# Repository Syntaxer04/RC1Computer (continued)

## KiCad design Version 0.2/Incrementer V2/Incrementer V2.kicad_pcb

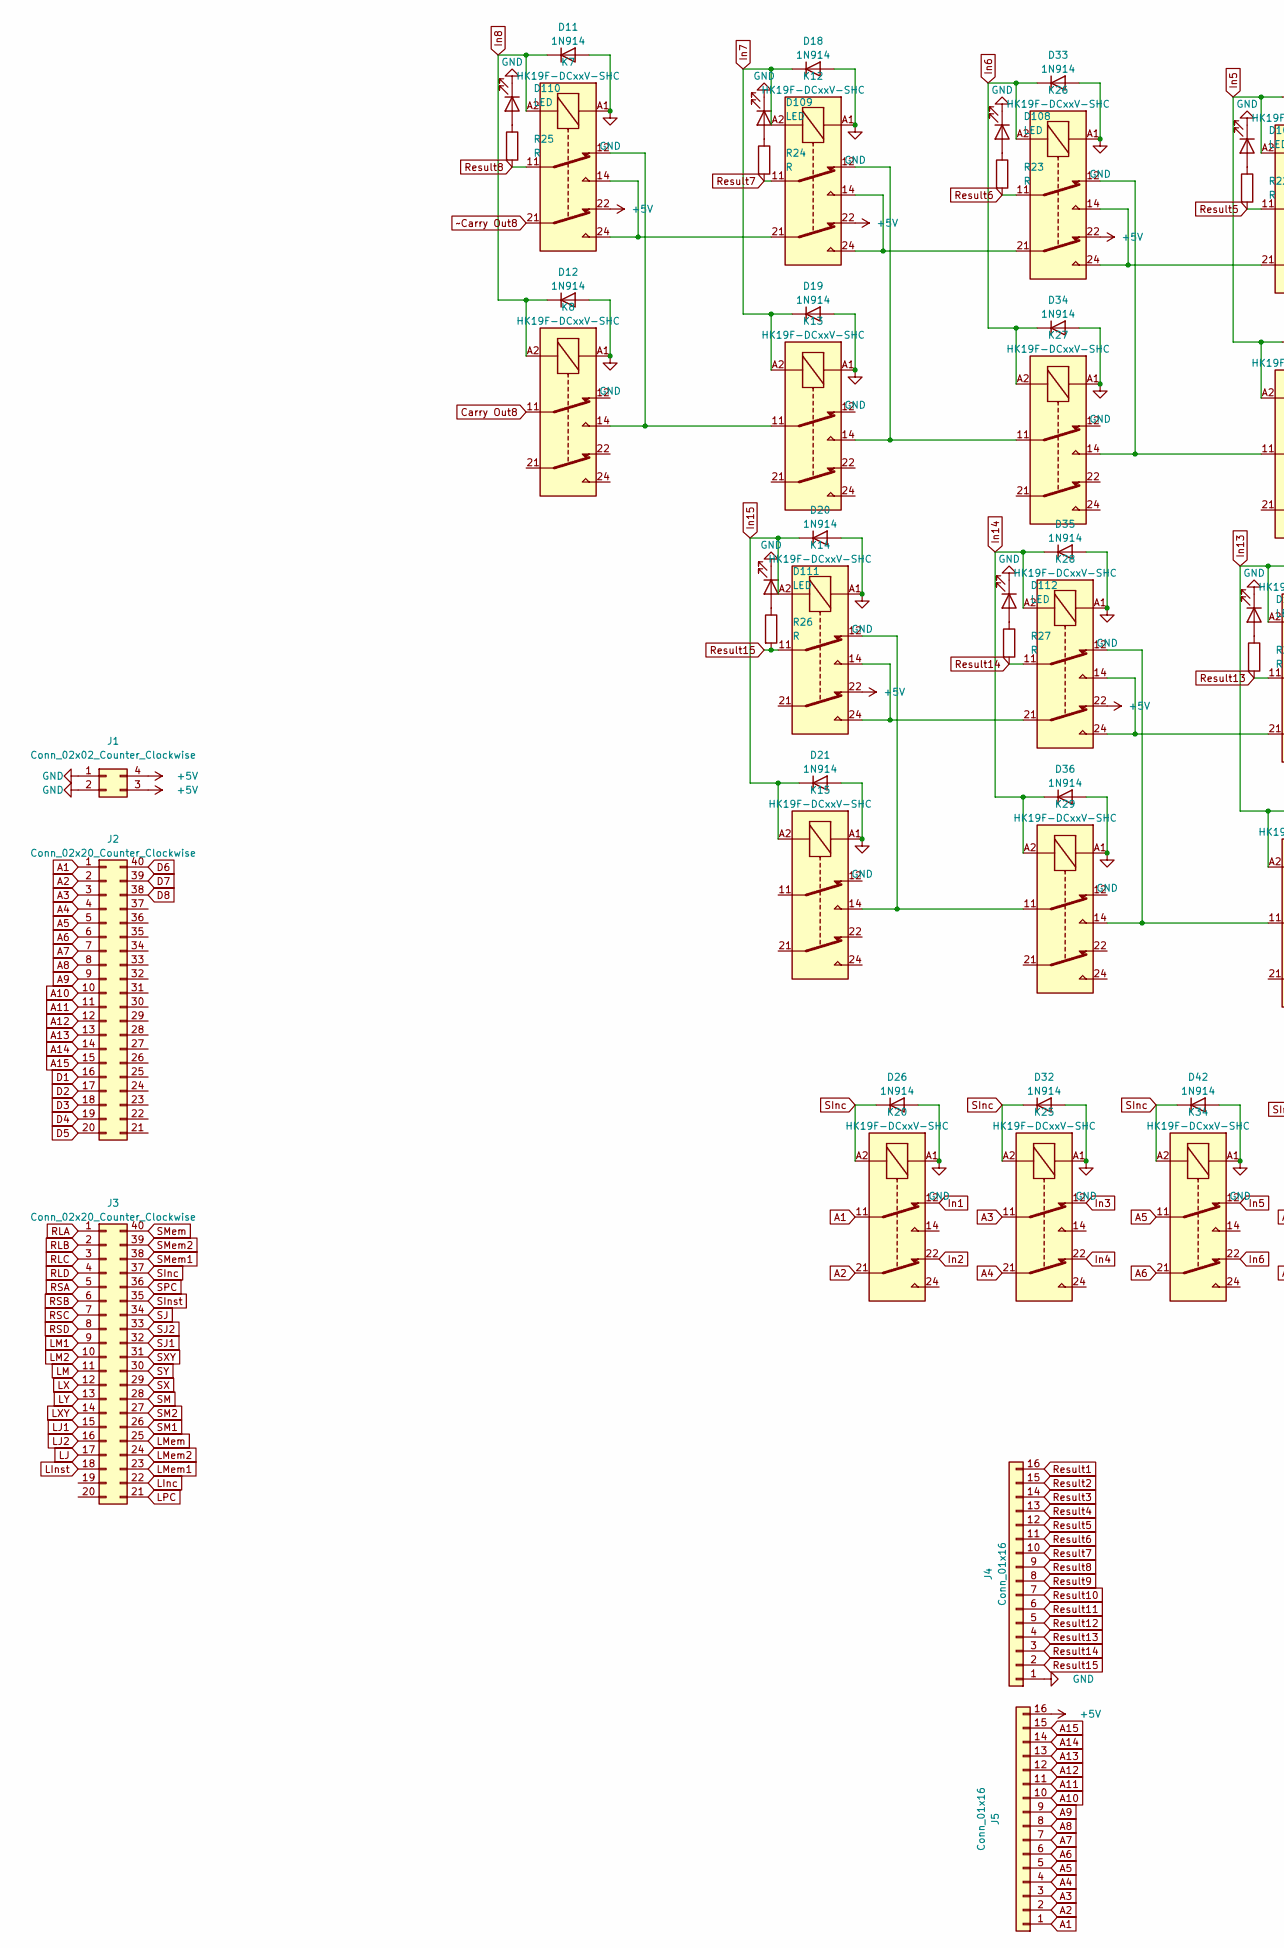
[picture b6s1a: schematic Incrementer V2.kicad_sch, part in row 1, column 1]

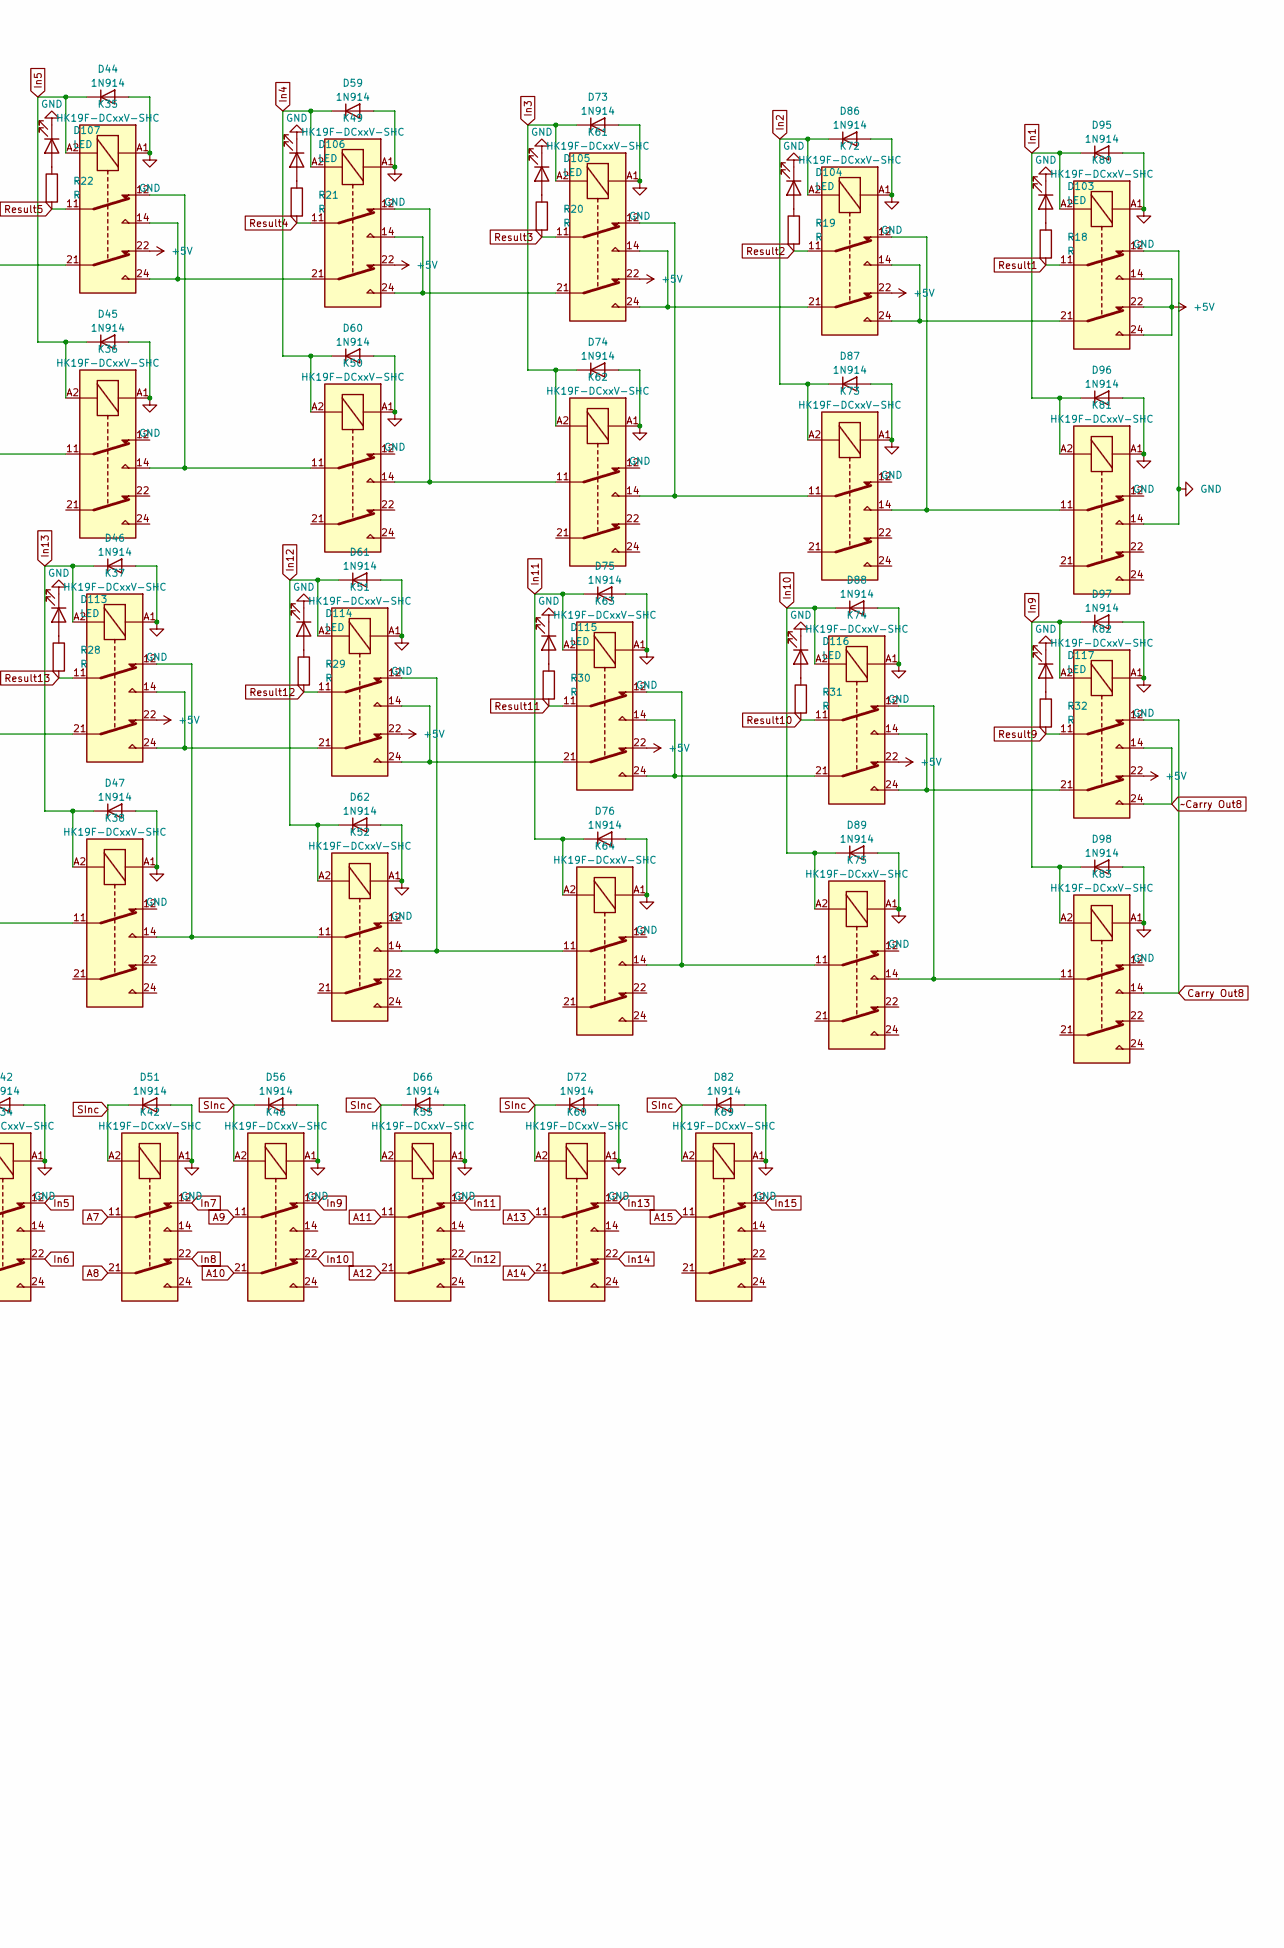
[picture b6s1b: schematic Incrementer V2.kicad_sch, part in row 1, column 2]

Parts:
D11, D12, D18, D19, D20, D21, D26, D32, D33, D34, D35, D36, D42, D44, D45, D46, D47, D51, D56, D59, D60, D61, D62, D66, D72, D73, D74, D75, D76, D82, D86, D87, D88, D89, D95, D96, D97, D98: 1N914; D_DO-35_SOD27_P7.62mm_Horizontal
D103, D104, D105, D106, D107, D108, D109, D110, D111, D112, D113, D114, D115, D116, D117: LED; LED_D5.0mm ohne SilkS
J1: Conn_02x02_Counter_Clockwise; PinSocket_2x02_P2.54mm_Horizontal
J2, J3: Conn_02x20_Counter_Clockwise; PinSocket_2x20_P2.54mm_Horizontal
J4, J5: Conn_01x16; PinHeader_1x16_P2.54mm_Vertical
K7, K8, K12, K13, K14, K15, K20, K25, K26, K27, K28, K29, K34, K35, K36, K37, K38, K42, K46, K49, K50, K51, K52, K55, K60, K61, K62, K63, K64, K69, K72, K73, K74, K75, K80, K81, K82, K83: HK19F-DCxxV-SHC; Relay_DPDT_Finder_30.22 ohne SilkS
R18, R19, R20, R21, R22, R23, R24, R25, R26, R27, R28, R29, R30, R31, R32: R; R_Axial_DIN0204_L3.6mm_D1.6mm_P7.62mm_Horizontal

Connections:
+5V: J1.3, J1.4, J5.16, K7.22, K12.22, K14.22, K26.22, K28.22, K35.22, K37.22, K49.22, K51.22, K61.22, K63.22, K72.22, K74.22, K80.14, K80.22, K80.24, K82.22
A1: J2.1, J5.1, K20.11
A2: J2.2, J5.2, K20.21
A3: J2.3, J5.3, K25.11
A4: J2.4, J5.4, K25.21
A5: J2.5, J5.5, K34.11
A6: J2.6, J5.6, K34.21
A7: J2.7, J5.7, K42.11
A8: J2.8, J5.8, K42.21
A9: J2.9, J5.9, K46.11
A10: J2.10, J5.10, K46.21
A11: J2.11, J5.11, K55.11
A12: J2.12, J5.12, K55.21
A13: J2.13, J5.13, K60.11
A14: J2.14, J5.14, K60.21
A15: J2.15, J5.15, K69.11
Carry Out8: K8.11, K82.12, K83.14
D1: J2.16
D2: J2.17
D3: J2.18
D4: J2.19
D5: J2.20
D6: J2.40
D7: J2.39
D8: J2.38
GND: D11.2 (A), D12.2 (A), D18.2 (A), D19.2 (A), D20.2 (A), D21.2 (A), D26.2 (A), D32.2 (A), D33.2 (A), D34.2 (A), D35.2 (A), D36.2 (A), D42.2 (A), D44.2 (A), D45.2 (A), D46.2 (A), D47.2 (A), D51.2 (A), D56.2 (A), D59.2 (A), D60.2 (A), D61.2 (A), D62.2 (A), D66.2 (A), D72.2 (A), D73.2 (A), D74.2 (A), D75.2 (A), D76.2 (A), D82.2 (A), D86.2 (A), D87.2 (A), D88.2 (A), D89.2 (A), D95.2 (A), D96.2 (A), D97.2 (A), D98.2 (A), D103.1 (K), D104.1 (K), D105.1 (K), D106.1 (K), D107.1 (K), D108.1 (K), D109.1 (K), D110.1 (K), D111.1 (K), D112.1 (K), D113.1 (K), D114.1 (K), D115.1 (K), D116.1 (K), D117.1 (K), J1.1, J1.2, J4.1, K7.A1, K8.A1, K12.A1, K13.A1, K14.A1, K15.A1, K20.A1, K25.A1, K26.A1, K27.A1, K28.A1, K29.A1, K34.A1, K35.A1, K36.A1, K37.A1, K38.A1, K42.A1, K46.A1, K49.A1, K50.A1, K51.A1, K52.A1, K55.A1, K60.A1, K61.A1, K62.A1, K63.A1, K64.A1, K69.A1, K72.A1, K73.A1, K74.A1, K75.A1, K80.12, K80.A1, K81.14, K81.A1, K82.A1, K83.A1
In1: D95.1 (K), D96.1 (K), K20.12, K80.A2, K81.A2
In2: D86.1 (K), D87.1 (K), K20.22, K72.A2, K73.A2
In3: D73.1 (K), D74.1 (K), K25.12, K61.A2, K62.A2
In4: D59.1 (K), D60.1 (K), K25.22, K49.A2, K50.A2
In5: D44.1 (K), D45.1 (K), K34.12, K35.A2, K36.A2
In6: D33.1 (K), D34.1 (K), K26.A2, K27.A2, K34.22
In7: D18.1 (K), D19.1 (K), K12.A2, K13.A2, K42.12
In8: D11.1 (K), D12.1 (K), K7.A2, K8.A2, K42.22
In9: D97.1 (K), D98.1 (K), K46.12, K82.A2, K83.A2
In10: D88.1 (K), D89.1 (K), K46.22, K74.A2, K75.A2
In11: D75.1 (K), D76.1 (K), K55.12, K63.A2, K64.A2
In12: D61.1 (K), D62.1 (K), K51.A2, K52.A2, K55.22
In13: D46.1 (K), D47.1 (K), K37.A2, K38.A2, K60.12
In14: D35.1 (K), D36.1 (K), K28.A2, K29.A2, K60.22
In15: D20.1 (K), D21.1 (K), K14.A2, K15.A2, K69.12
LInc: J3.22
LInst: J3.18
LJ1: J3.15
LJ2: J3.16
LJ: J3.17
LM: J3.11
LM1: J3.9
LM2: J3.10
LMem: J3.25
LMem1: J3.23
LMem2: J3.24
LPC: J3.21
LX: J3.12
LXY: J3.14
LY: J3.13
unnamed: D103.2 (A), R18.1
unnamed: D104.2 (A), R19.1
unnamed: D105.2 (A), R20.1
unnamed: D106.2 (A), R21.1
unnamed: D107.2 (A), R22.1
unnamed: D108.2 (A), R23.1
unnamed: D109.2 (A), R24.1
unnamed: D110.2 (A), R25.1
unnamed: D111.2 (A), R26.1
unnamed: D112.2 (A), R27.1
unnamed: D113.2 (A), R28.1
unnamed: D114.2 (A), R29.1
unnamed: D115.2 (A), R30.1
unnamed: D116.2 (A), R31.1
unnamed: D117.2 (A), R32.1
unnamed: K12.12, K13.14, K27.11
unnamed: K12.14, K12.24, K26.21
unnamed: K7.14, K7.24, K12.21
unnamed: K7.12, K8.14, K13.11
unnamed: K14.12, K15.14, K29.11
unnamed: K14.14, K14.24, K28.21
unnamed: K26.12, K27.14, K36.11
unnamed: K26.14, K26.24, K35.21
unnamed: K28.12, K29.14, K38.11
unnamed: K28.14, K28.24, K37.21
unnamed: K35.12, K36.14, K50.11
unnamed: K35.14, K35.24, K49.21
unnamed: K37.12, K38.14, K52.11
unnamed: K37.14, K37.24, K51.21
unnamed: K49.12, K50.14, K62.11
unnamed: K49.14, K49.24, K61.21
unnamed: K51.12, K52.14, K64.11
unnamed: K51.14, K51.24, K63.21
unnamed: K61.12, K62.14, K73.11
unnamed: K61.14, K61.24, K72.21
unnamed: K63.12, K64.14, K75.11
unnamed: K63.14, K63.24, K74.21
unnamed: K72.12, K73.14, K81.11
unnamed: K72.14, K72.24, K80.21
unnamed: K74.12, K75.14, K83.11
unnamed: K74.14, K74.24, K82.21
RLA: J3.1
RLB: J3.2
RLC: J3.3
RLD: J3.4
RSA: J3.5
RSB: J3.6
RSC: J3.7
RSD: J3.8
Result1: J4.16, K80.11, R18.2
Result2: J4.15, K72.11, R19.2
Result3: J4.14, K61.11, R20.2
Result4: J4.13, K49.11, R21.2
Result5: J4.12, K35.11, R22.2
Result6: J4.11, K26.11, R23.2
Result7: J4.10, K12.11, R24.2
Result8: J4.9, K7.11, R25.2
Result9: J4.8, K82.11, R32.2
Result10: J4.7, K74.11, R31.2
Result11: J4.6, K63.11, R30.2
Result12: J4.5, K51.11, R29.2
Result13: J4.4, K37.11, R28.2
Result14: J4.3, K28.11, R27.2
Result15: J4.2, K14.11, R26.2
SInc: D26.1 (K), D32.1 (K), D42.1 (K), D51.1 (K), D56.1 (K), D66.1 (K), D72.1 (K), D82.1 (K), J3.37, K20.A2, K25.A2, K34.A2, K42.A2, K46.A2, K55.A2, K60.A2, K69.A2
SInst: J3.35
SJ1: J3.32
SJ2: J3.33
SJ: J3.34
SM: J3.28
SM1: J3.26
SM2: J3.27
SMem: J3.40
SMem1: J3.38
SMem2: J3.39
SPC: J3.36
SX: J3.29
SXY: J3.31
SY: J3.30
~Carry Out8: K7.21, K82.14, K82.24

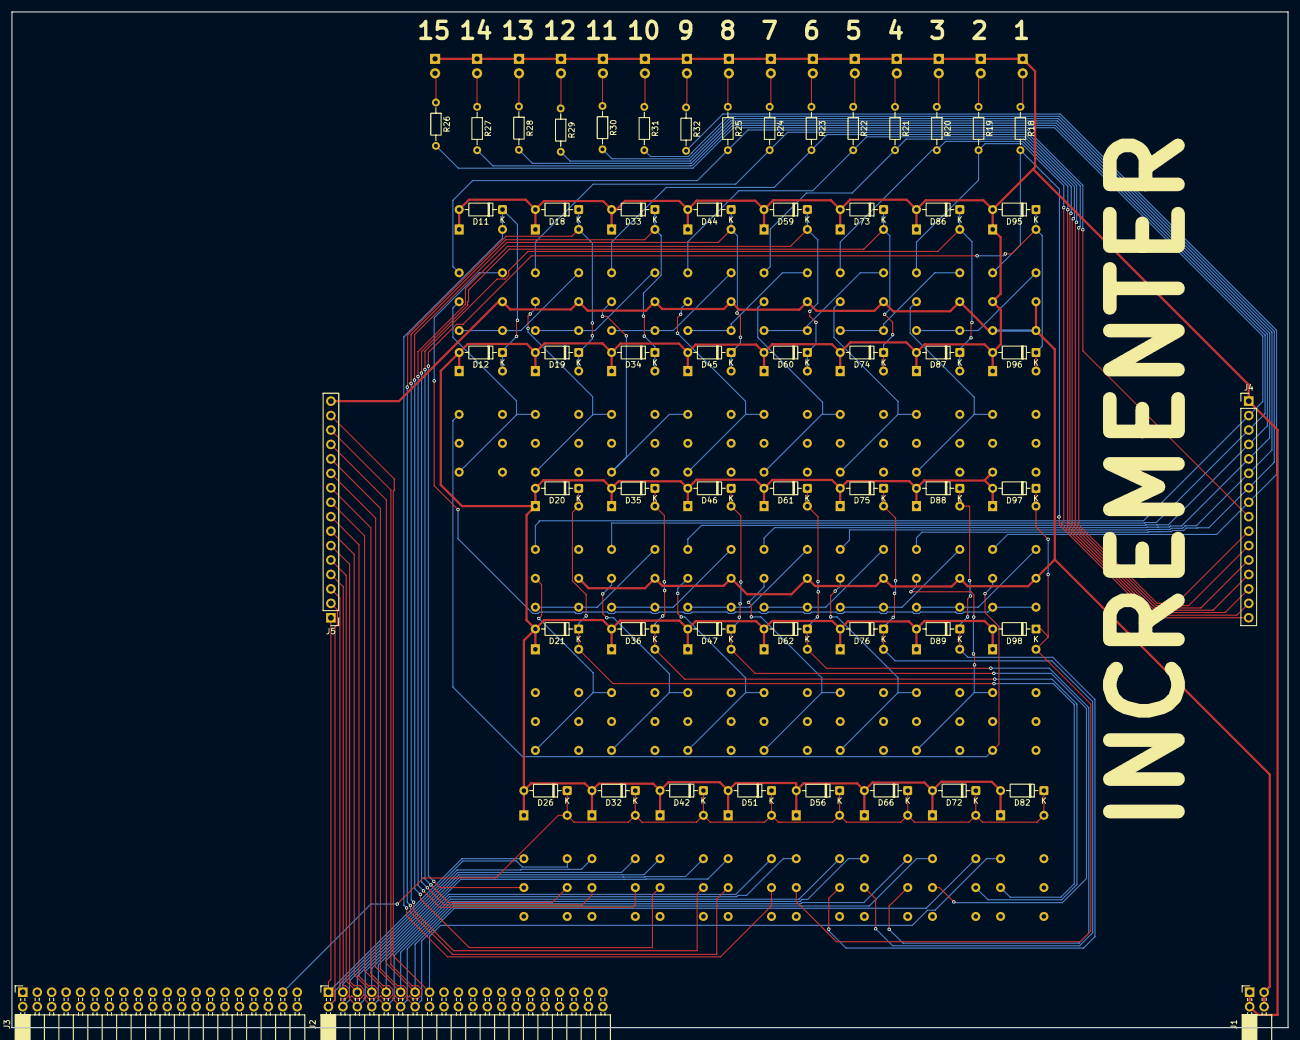
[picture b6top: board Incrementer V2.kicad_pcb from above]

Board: 2 copper layers, 224.4 x 178.6 mm, 111 parts (0 on the bottom side), 91 nets.

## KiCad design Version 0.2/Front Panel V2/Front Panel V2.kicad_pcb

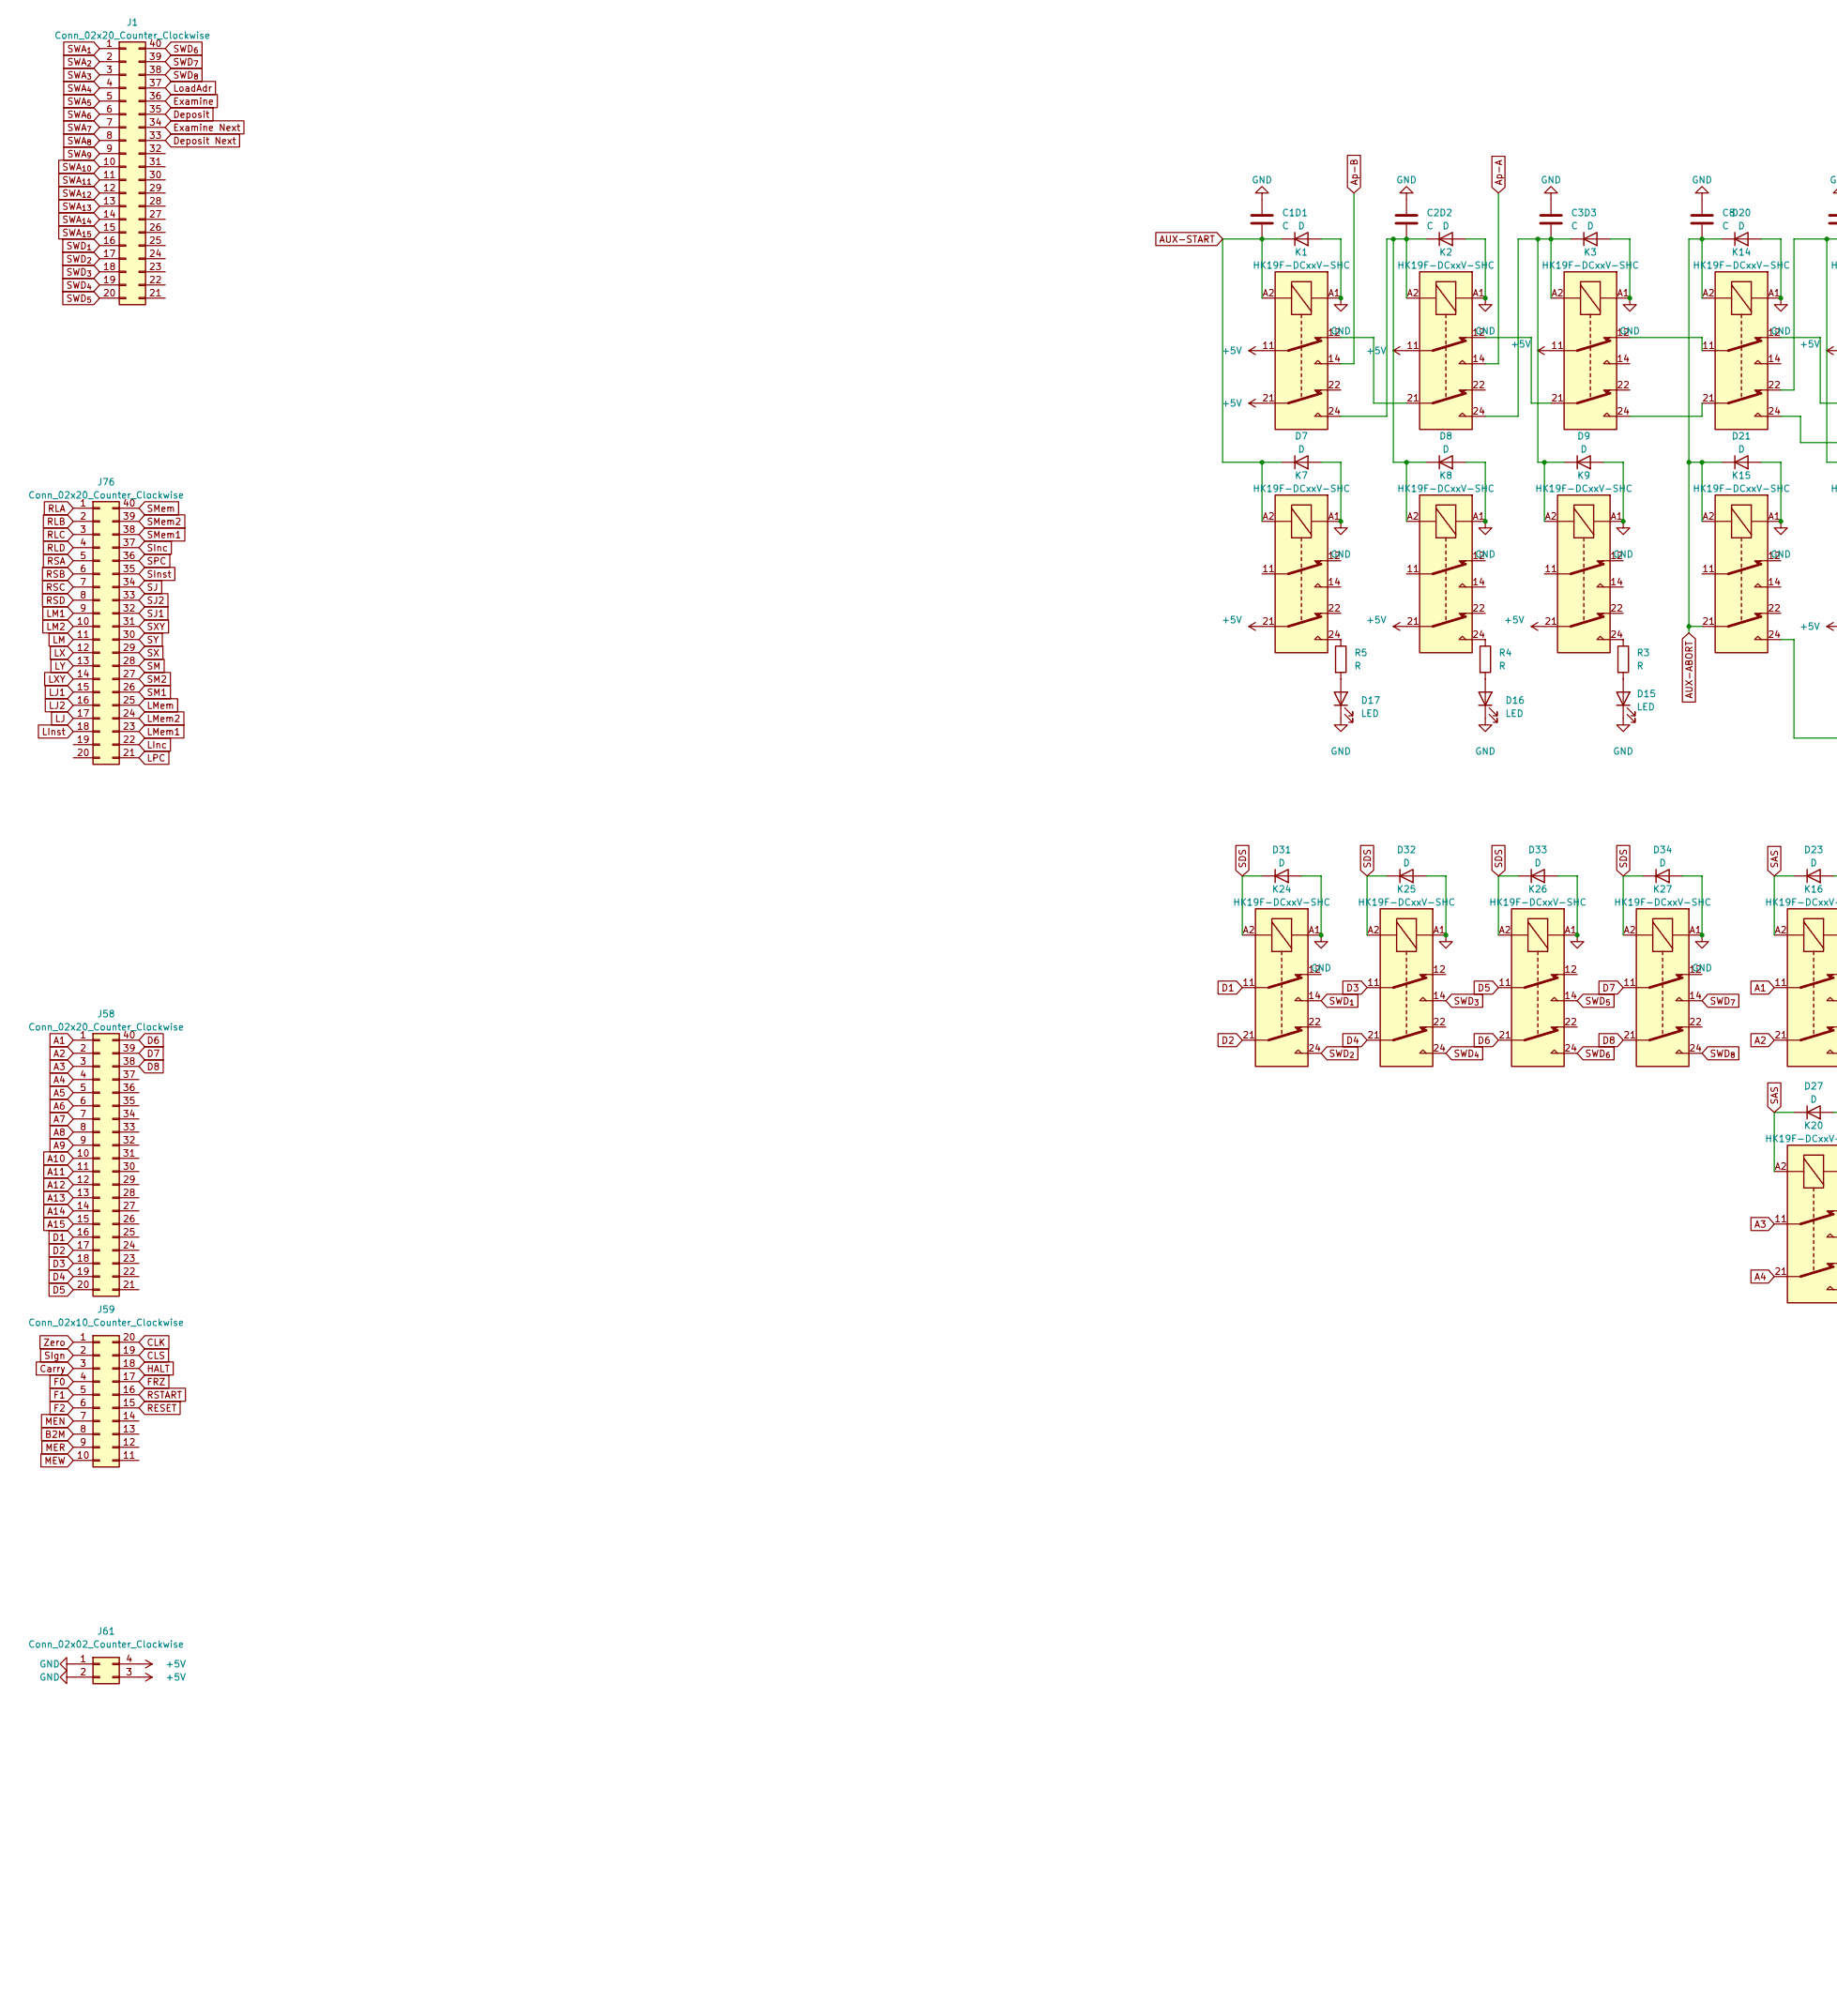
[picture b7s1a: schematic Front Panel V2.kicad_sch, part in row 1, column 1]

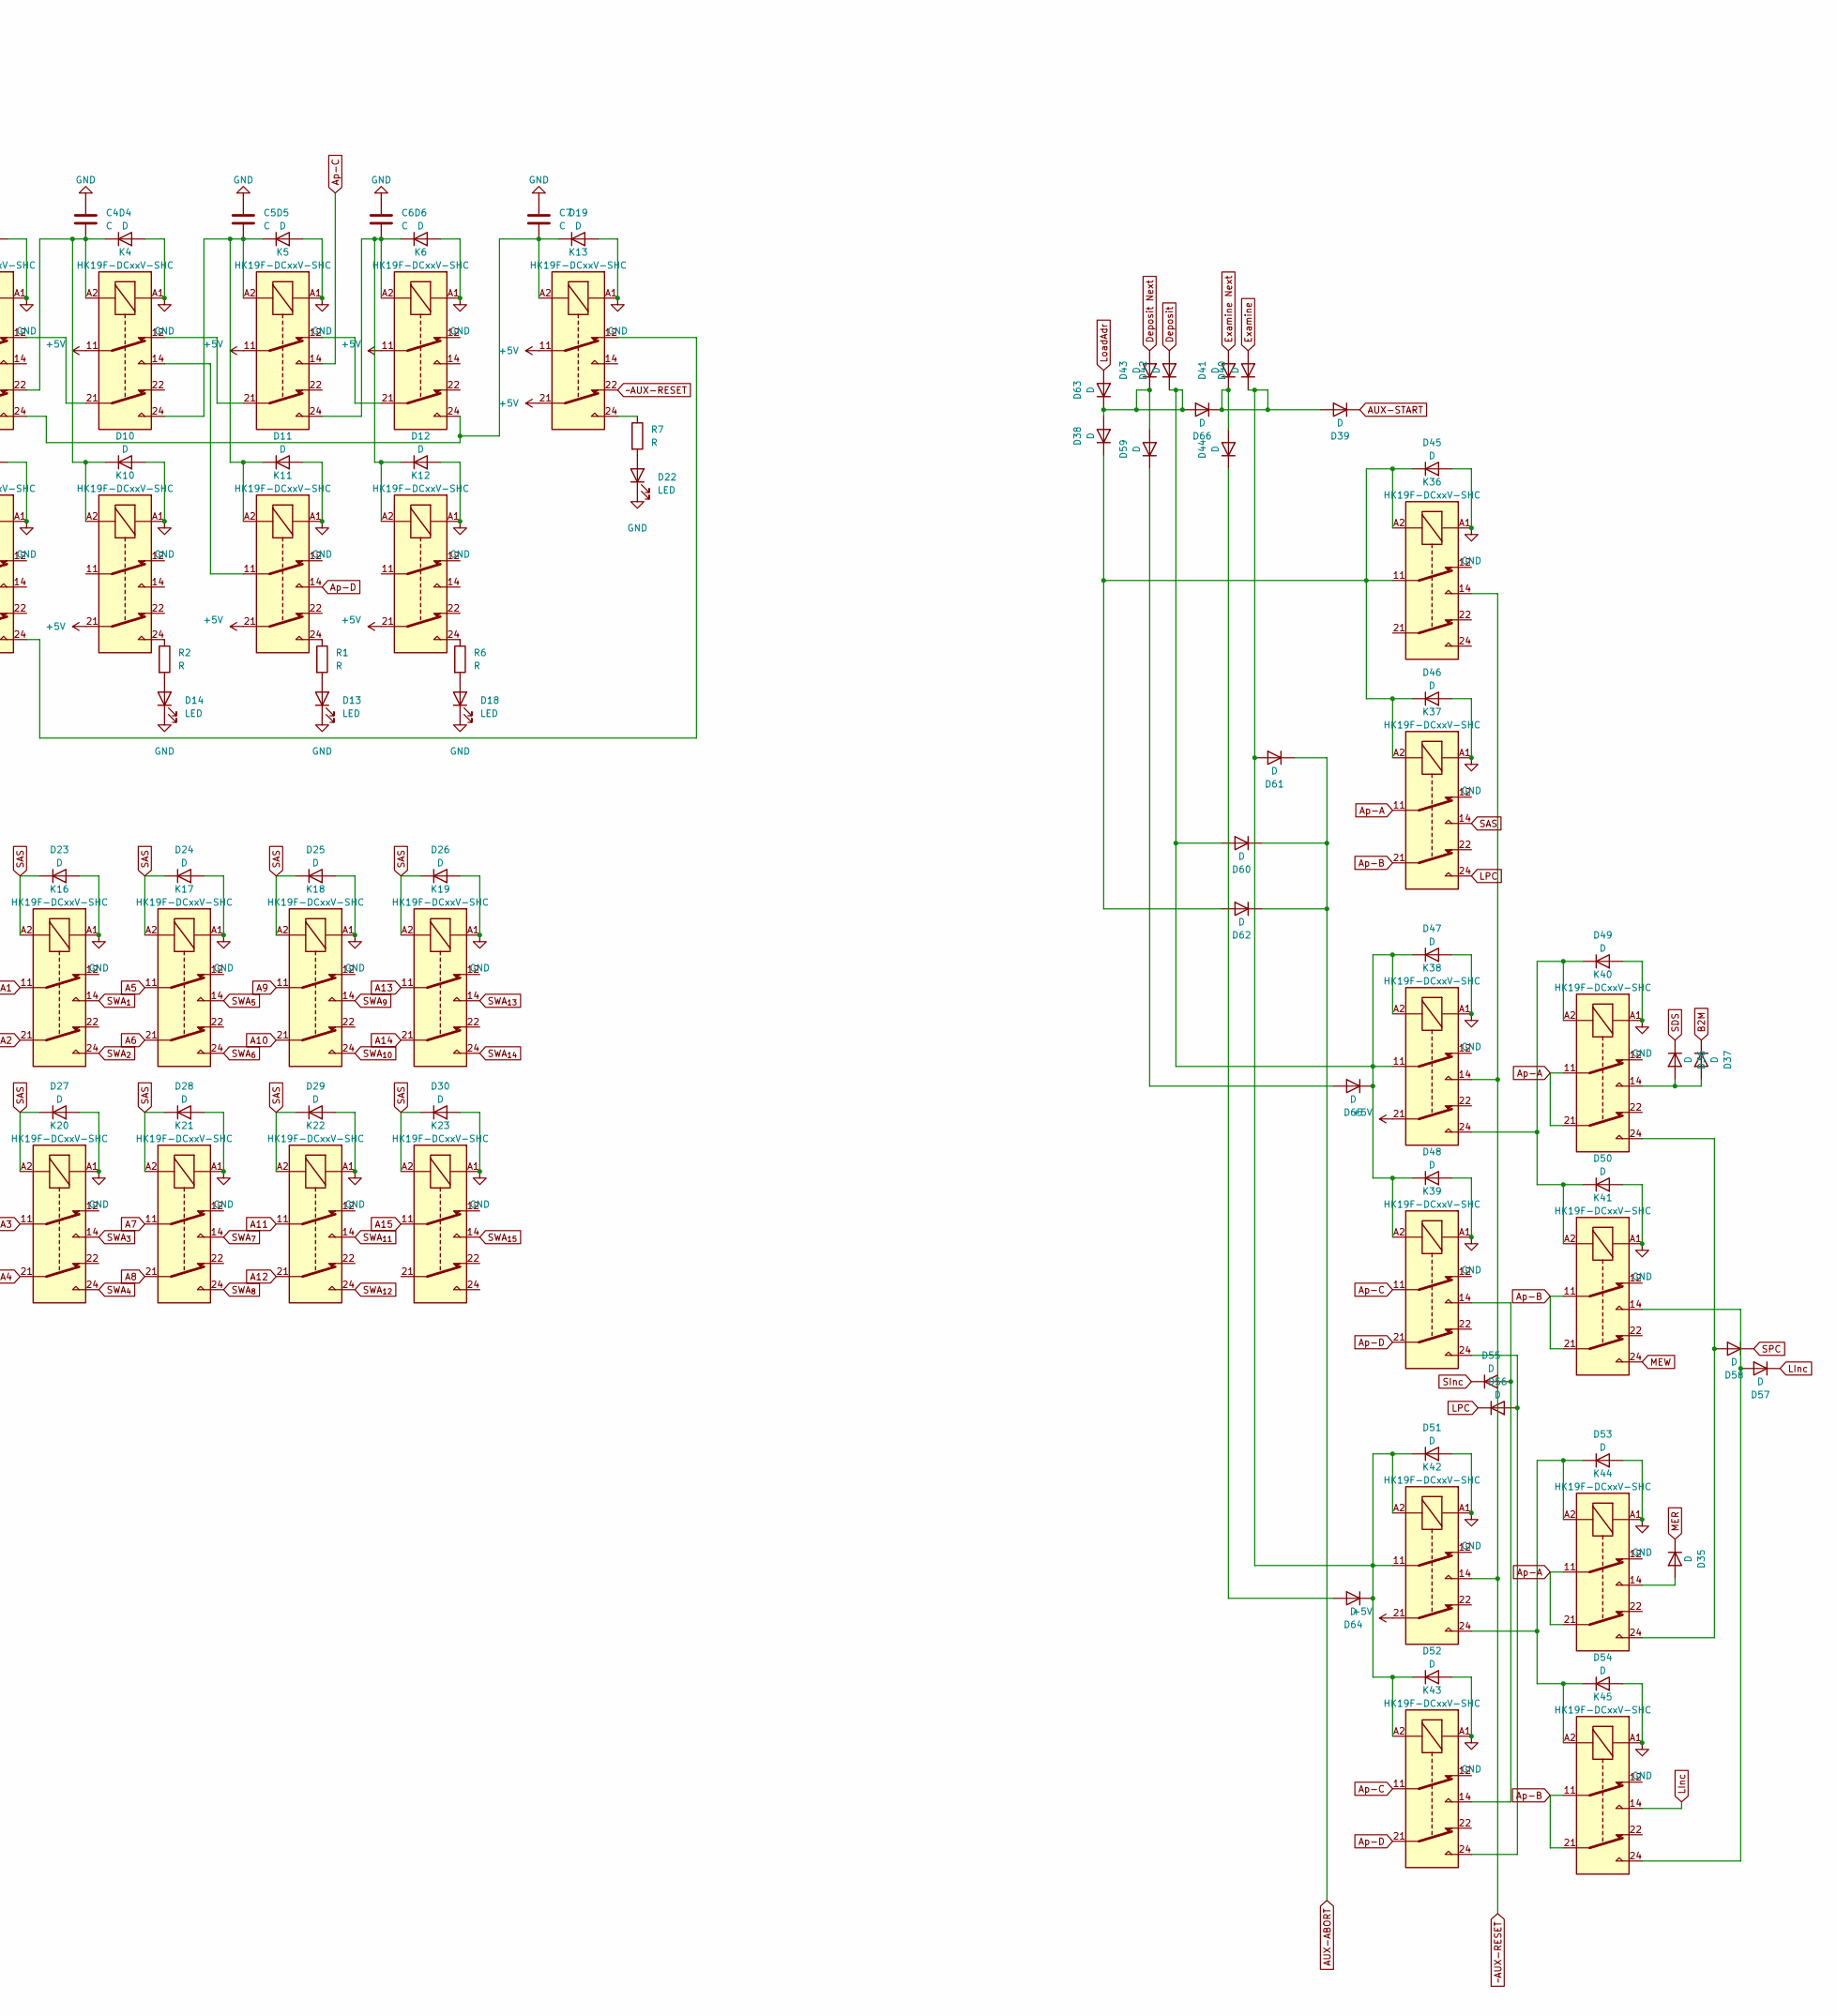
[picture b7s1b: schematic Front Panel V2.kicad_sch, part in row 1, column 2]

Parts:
C1, C2, C3, C4, C5, C6, C7, C8: C; C_Radial_D6.3mm_H5.0mm_P2.50mm
D1, D2, D3, D4, D5, D6, D7, D8, D9, D10, D11, D12, D19, D20, D21, D23, D24, D25, D26, D27, D28, D29, D30, D31, D32, D33, D34, D35, D36, D37, D38, D39, D40, D41, D42, D43, D44, D45, D46, D47, D48, D49, D50, D51, D52, D53, D54, D55, D56, D57, D58, D59, D60, D61, D62, D63, D64, D65, D66: D; D_DO-35_SOD27_P7.62mm_Horizontal
D13, D14, D15, D16, D17, D18, D22: LED; LED_D5.0mm
J1: Conn_02x20_Counter_Clockwise; PinSocket_2x20_P2.54mm_Vertical
J58, J76: Conn_02x20_Counter_Clockwise; PinSocket_2x20_P2.54mm_Horizontal
J59: Conn_02x10_Counter_Clockwise; PinSocket_2x10_P2.54mm_Horizontal
J61: Conn_02x02_Counter_Clockwise; PinSocket_2x02_P2.54mm_Horizontal
K1, K2, K3, K4, K5, K6, K7, K8, K9, K10, K11, K12, K13, K14, K15, K16, K17, K18, K19, K20, K21, K22, K23, K24, K25, K26, K27, K36, K37, K38, K39, K40, K41, K42, K43, K44, K45: HK19F-DCxxV-SHC; Relay_DPDT_Finder_30.22 ohne SilkS
R1, R2, R3, R4, R5, R6, R7: R; R_Axial_DIN0207_L6.3mm_D2.5mm_P7.62mm_Horizontal

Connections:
+5V: J61.3, J61.4, K1.11, K1.21, K2.11, K3.11, K4.11, K5.11, K6.11, K7.21, K8.21, K9.21, K10.21, K11.21, K12.21, K13.11, K13.21, K38.21, K42.21
A1: J58.1, K16.11
A2: J58.2, K16.21
A3: J58.3, K20.11
A4: J58.4, K20.21
A5: J58.5, K17.11
A6: J58.6, K17.21
A7: J58.7, K21.11
A8: J58.8, K21.21
A9: J58.9, K18.11
A10: J58.10, K18.21
A11: J58.11, K22.11
A12: J58.12, K22.21
A13: J58.13, K19.11
A14: J58.14, K19.21
A15: J58.15, K23.11
AUX-ABORT: C8.2, D20.1 (K), D21.1 (K), D60.1 (K), D61.1 (K), D62.1 (K), K14.A2, K15.21, K15.A2
AUX-START: C1.2, D1.1 (K), D7.1 (K), D39.1 (K), K1.A2, K7.A2
Ap-A: K2.14, K37.11, K40.11, K40.21, K44.11, K44.21
Ap-B: K1.14, K37.21, K41.11, K41.21, K45.11, K45.21
Ap-C: K5.14, K39.11, K43.11
Ap-D: K11.14, K39.21, K43.21
B2M: D37.1 (K), J59.8
D1: J58.16, K24.11
D2: J58.17, K24.21
D3: J58.18, K25.11
D4: J58.19, K25.21
D5: J58.20, K26.11
D6: J58.40, K26.21
D7: J58.39, K27.11
D8: J58.38, K27.21
Deposit: D42.2 (A), J1.35
Deposit Next: D43.2 (A), J1.33
Examine: D40.2 (A), J1.36
Examine Next: D41.2 (A), J1.34
GND: C1.1, C2.1, C3.1, C4.1, C5.1, C6.1, C7.1, C8.1, D1.2 (A), D2.2 (A), D3.2 (A), D4.2 (A), D5.2 (A), D6.2 (A), D7.2 (A), D8.2 (A), D9.2 (A), D10.2 (A), D11.2 (A), D12.2 (A), D13.1 (K), D14.1 (K), D15.1 (K), D16.1 (K), D17.1 (K), D18.1 (K), D19.2 (A), D20.2 (A), D21.2 (A), D22.1 (K), D23.2 (A), D24.2 (A), D25.2 (A), D26.2 (A), D27.2 (A), D28.2 (A), D29.2 (A), D30.2 (A), D31.2 (A), D32.2 (A), D33.2 (A), D34.2 (A), D45.2 (A), D46.2 (A), D47.2 (A), D48.2 (A), D49.2 (A), D50.2 (A), D51.2 (A), D52.2 (A), D53.2 (A), D54.2 (A), J61.1, J61.2, K1.A1, K2.A1, K3.A1, K4.A1, K5.A1, K6.A1, K7.A1, K8.A1, K9.A1, K10.A1, K11.A1, K12.A1, K13.A1, K14.A1, K15.A1, K16.A1, K17.A1, K18.A1, K19.A1, K20.A1, K21.A1, K22.A1, K23.A1, K24.A1, K25.A1, K26.A1, K27.A1, K36.A1, K37.A1, K38.A1, K39.A1, K40.A1, K41.A1, K42.A1, K43.A1, K44.A1, K45.A1
LInc: D57.1 (K), J76.22, K45.14
LPC: D56.1 (K), J76.21, K37.24
LoadAdr: D63.2 (A), J1.37
MER: D35.1 (K), J59.9
MEW: J59.10, K41.24
unnamed: C2.2, D2.1 (K), D8.1 (K), K1.24, K2.A2, K8.A2
unnamed: C3.2, D3.1 (K), D9.1 (K), K2.24, K3.A2, K9.A2
unnamed: C4.2, D4.1 (K), D10.1 (K), K4.A2, K10.A2, K14.22
unnamed: C5.2, D5.1 (K), D11.1 (K), K4.24, K5.A2, K11.A2
unnamed: C6.2, D6.1 (K), D12.1 (K), K5.24, K6.A2, K12.A2
unnamed: D13.2 (A), R1.2
unnamed: D14.2 (A), R2.2
unnamed: D15.2 (A), R3.2
unnamed: D16.2 (A), R4.2
unnamed: D17.2 (A), R5.2
unnamed: D18.2 (A), R6.2
unnamed: C7.2, D19.1 (K), K6.24, K13.A2, K14.24
unnamed: D22.2 (A), R7.2
unnamed: D35.2 (A), K44.14
unnamed: D36.2 (A), D37.2 (A), K40.14
unnamed: D38.2 (A), D42.1 (K), D43.1 (K), D47.1 (K), D48.1 (K), D59.2 (A), D60.2 (A), D63.1 (K), D65.1 (K), D66.2 (A), K38.11, K38.A2, K39.A2
unnamed: D38.1 (K), D45.1 (K), D46.1 (K), D62.2 (A), K36.11, K36.A2, K37.A2
unnamed: D39.2 (A), D40.1 (K), D41.1 (K), D44.2 (A), D51.1 (K), D52.1 (K), D61.2 (A), D64.1 (K), D66.1 (K), K42.11, K42.A2, K43.A2
unnamed: D44.1 (K), D64.2 (A)
unnamed: D49.1 (K), D50.1 (K), K38.24, K40.A2, K41.A2
unnamed: D53.1 (K), D54.1 (K), K42.24, K44.A2, K45.A2
unnamed: D55.2 (A), K39.14, K43.14
unnamed: D56.2 (A), K39.24, K43.24
unnamed: D57.2 (A), K41.14, K45.24
unnamed: D58.2 (A), K40.24, K44.24
unnamed: D59.1 (K), D65.2 (A)
unnamed: K1.12, K2.21
unnamed: K2.12, K3.21
unnamed: K4.12, K5.21
unnamed: K5.12, K6.21
unnamed: K7.24, R5.1
unnamed: K8.24, R4.1
unnamed: K9.24, R3.1
unnamed: K10.24, R2.1
unnamed: K4.14, K11.11
unnamed: K11.24, R1.1
unnamed: K12.24, R6.1
unnamed: K13.12, K15.24
unnamed: K13.24, R7.1
unnamed: K3.12, K14.11
unnamed: K4.21, K14.12
unnamed: K3.24, K14.21
SAS: D23.1 (K), D24.1 (K), D25.1 (K), D26.1 (K), D27.1 (K), D28.1 (K), D29.1 (K), D30.1 (K), K16.A2, K17.A2, K18.A2, K19.A2, K20.A2, K21.A2, K22.A2, K23.A2, K37.14
SDS: D31.1 (K), D32.1 (K), D33.1 (K), D34.1 (K), D36.1 (K), K24.A2, K25.A2, K26.A2, K27.A2
SInc: D55.1 (K), J76.37
SPC: D58.1 (K), J76.36
SWA_{1}: J1.1, K16.14
SWA_{2}: J1.2, K16.24
SWA_{3}: J1.3, K20.14
SWA_{4}: J1.4, K20.24
SWA_{5}: J1.5, K17.14
SWA_{6}: J1.6, K17.24
SWA_{7}: J1.7, K21.14
SWA_{8}: J1.8, K21.24
SWA_{9}: J1.9, K18.14
SWA_{10}: J1.10, K18.24
SWA_{11}: J1.11, K22.14
SWA_{12}: J1.12, K22.24
SWA_{13}: J1.13, K19.14
SWA_{14}: J1.14, K19.24
SWA_{15}: J1.15, K23.14
SWD_{1}: J1.16, K24.14
SWD_{2}: J1.17, K24.24
SWD_{3}: J1.18, K25.14
SWD_{4}: J1.19, K25.24
SWD_{5}: J1.20, K26.14
SWD_{6}: J1.40, K26.24
SWD_{7}: J1.39, K27.14
SWD_{8}: J1.38, K27.24
~AUX-RESET: K13.22, K36.14, K38.14, K42.14
